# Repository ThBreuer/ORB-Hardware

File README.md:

# ORB-Hardware
OpenRoboticBoard: schematics, layout and documentation

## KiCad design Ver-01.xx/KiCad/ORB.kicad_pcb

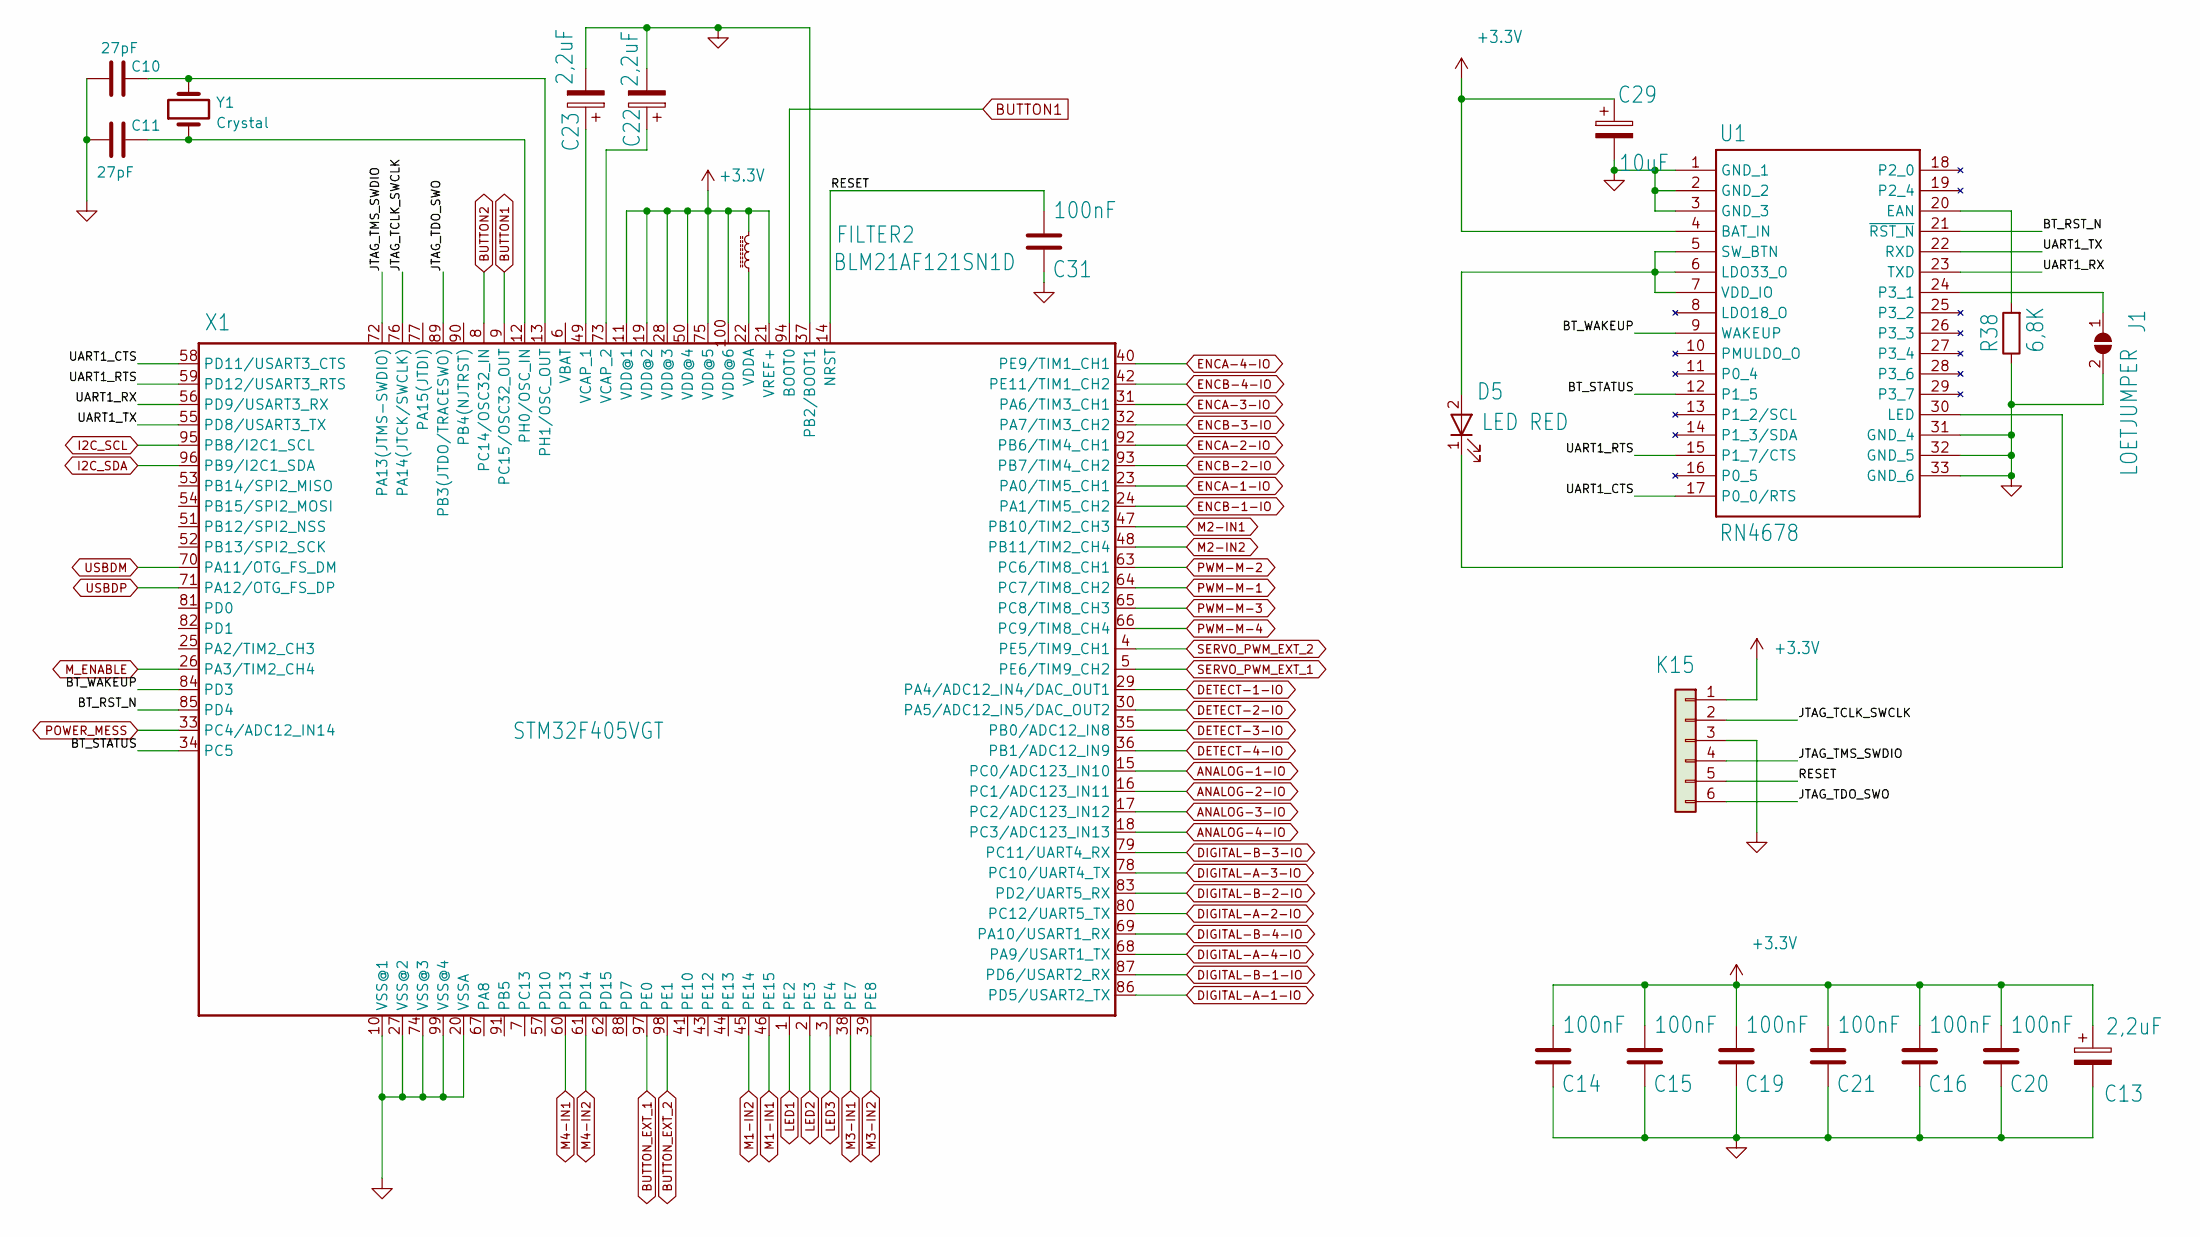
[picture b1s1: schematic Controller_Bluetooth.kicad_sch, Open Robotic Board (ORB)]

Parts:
C10, C11: 27pF; C_0805_2012Metric; MPN C0805C270K8HAC7800
C13, C22, C23: 2,2uF; CP_EIA-3216-10_Kemet-I; MPN T491A225K016AT
C14, C15, C16, C19, C20, C21, C31: 100nF; C_0805_2012Metric; MPN C0805C104K5RAC7800
C29: 10uF; CP_EIA-3528-12_Kemet-T; MPN T491B106M025AT
D5: LED RED; LED_0805_2012Metric; MPN QTLP630C7TR
FILTER2: BLM21AF121SN1D; L_0805_2012Metric; MPN BLM21AG121SN1D
J1: LOETJUMPER; SolderJumper-2_P1.3mm_Open_Pad1.0x1.5mm; MPN not mounted
K15: Stiftleiste_1x06; PinHeader_1x06_P2.54mm_Vertical; MPN not mounted
R38: 6,8K; R_0603_1608Metric; MPN RC0603FR-136K8L
U1: RN4678; MODULE_RN4678-V_RM100; MPN RN4678-V/RM113
X1: STM32F405VGT; LQFP-100_14x14mm_P0.5mm; MPN STM32F405VGT6
Y1: Crystal; Crystal_SMD_Abracon_ABM3-2Pin_5.0x3.2mm; MPN ECS-80-18-30-JGN-TR

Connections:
+3V3: C13.1, C14.2, C15.2, C16.2, C19.2, C20.2, C21.2, C29.1, FILTER2.2, K15.1, U1.4 (BAT_IN), X1.11 (VDD@1), X1.19 (VDD@2), X1.21 (VREF+), X1.28 (VDD@3), X1.50 (VDD@4), X1.75 (VDD@5), X1.100 (VDD@6); also elsewhere on the board
/Controller, Bluetooth/BT_RST_N: U1.21 (~RST_N), X1.85 (PD4)
/Controller, Bluetooth/BT_STATUS: U1.12 (P1_5), X1.34 (PC5)
/Controller, Bluetooth/BT_WAKEUP: U1.9 (WAKEUP), X1.84 (PD3)
/Controller, Bluetooth/JTAG_TCLK_SWCLK: K15.2, X1.76 (PA14(JTCK/SWCLK))
/Controller, Bluetooth/JTAG_TDO_SWO: K15.6, X1.89 (PB3(JTDO/TRACESWO))
/Controller, Bluetooth/JTAG_TMS_SWDIO: K15.4, X1.72 (PA13(JTMS-SWDIO))
/Controller, Bluetooth/RESET: C31.2, K15.5, X1.14 (NRST)
/Controller, Bluetooth/UART1_CTS: U1.17 (P0_0/RTS), X1.58 (PD11/USART3_CTS)
/Controller, Bluetooth/UART1_RTS: U1.15 (P1_7/CTS), X1.59 (PD12/USART3_RTS)
/Controller, Bluetooth/UART1_RX: U1.23 (TXD), X1.56 (PD9/USART3_RX)
/Controller, Bluetooth/UART1_TX: U1.22 (RXD), X1.55 (PD8/USART3_TX)
ANALOG-1-IO: X1.15 (PC0/ADC123_IN10); also elsewhere on the board
ANALOG-2-IO: X1.16 (PC1/ADC123_IN11); also elsewhere on the board
ANALOG-3-IO: X1.17 (PC2/ADC123_IN12); also elsewhere on the board
ANALOG-4-IO: X1.18 (PC3/ADC123_IN13); also elsewhere on the board
BUTTON1: X1.9 (PC15/OSC32_OUT), X1.94 (BOOT0); also elsewhere on the board
BUTTON2: X1.8 (PC14/OSC32_IN); also elsewhere on the board
BUTTON_EXT_1: X1.97 (PE0); also elsewhere on the board
BUTTON_EXT_2: X1.98 (PE1); also elsewhere on the board
DETECT-1-IO: X1.29 (PA4/ADC12_IN4/DAC_OUT1); also elsewhere on the board
DETECT-2-IO: X1.30 (PA5/ADC12_IN5/DAC_OUT2); also elsewhere on the board
DETECT-3-IO: X1.35 (PB0/ADC12_IN8); also elsewhere on the board
DETECT-4-IO: X1.36 (PB1/ADC12_IN9); also elsewhere on the board
DIGITAL-A-1-IO: X1.86 (PD5/USART2_TX); also elsewhere on the board
DIGITAL-A-2-IO: X1.80 (PC12/UART5_TX); also elsewhere on the board
DIGITAL-A-3-IO: X1.78 (PC10/UART4_TX); also elsewhere on the board
DIGITAL-A-4-IO: X1.68 (PA9/USART1_TX); also elsewhere on the board
DIGITAL-B-1-IO: X1.87 (PD6/USART2_RX); also elsewhere on the board
DIGITAL-B-2-IO: X1.83 (PD2/UART5_RX); also elsewhere on the board
DIGITAL-B-3-IO: X1.79 (PC11/UART4_RX); also elsewhere on the board
DIGITAL-B-4-IO: X1.69 (PA10/USART1_RX); also elsewhere on the board
ENCA-1-IO: X1.23 (PA0/TIM5_CH1); also elsewhere on the board
ENCA-2-IO: X1.92 (PB6/TIM4_CH1); also elsewhere on the board
ENCA-3-IO: X1.31 (PA6/TIM3_CH1); also elsewhere on the board
ENCA-4-IO: X1.40 (PE9/TIM1_CH1); also elsewhere on the board
ENCB-1-IO: X1.24 (PA1/TIM5_CH2); also elsewhere on the board
ENCB-2-IO: X1.93 (PB7/TIM4_CH2); also elsewhere on the board
ENCB-3-IO: X1.32 (PA7/TIM3_CH2); also elsewhere on the board
ENCB-4-IO: X1.42 (PE11/TIM1_CH2); also elsewhere on the board
GND: C10.1, C11.1, C13.2, C14.1, C15.1, C16.1, C19.1, C20.1, C21.1, C22.2, C23.2, C29.2, C31.1, J1.2 (B), K15.3, R38.1, U1.1 (GND_1), U1.2 (GND_2), U1.3 (GND_3), U1.31 (GND_4), U1.32 (GND_5), U1.33 (GND_6), X1.10 (VSS@1), X1.20 (VSSA), X1.27 (VSS@2), X1.37 (PB2/BOOT1), X1.74 (VSS@3), X1.99 (VSS@4); also elsewhere on the board
I2C_SCL: X1.95 (PB8/I2C1_SCL); also elsewhere on the board
I2C_SDA: X1.96 (PB9/I2C1_SDA); also elsewhere on the board
LED1: X1.1 (PE2); also elsewhere on the board
LED2: X1.2 (PE3); also elsewhere on the board
LED3: X1.3 (PE4); also elsewhere on the board
M1-IN1: X1.46 (PE15); also elsewhere on the board
M1-IN2: X1.45 (PE14); also elsewhere on the board
M2-IN1: X1.47 (PB10/TIM2_CH3); also elsewhere on the board
M2-IN2: X1.48 (PB11/TIM2_CH4); also elsewhere on the board
M3-IN1: X1.38 (PE7); also elsewhere on the board
M3-IN2: X1.39 (PE8); also elsewhere on the board
M4-IN1: X1.60 (PD13); also elsewhere on the board
M4-IN2: X1.61 (PD14); also elsewhere on the board
M_ENABLE: X1.26 (PA3/TIM2_CH4); also elsewhere on the board
unnamed: D5.2 (A), U1.5 (SW_BTN), U1.6 (LDO33_O), U1.7 (VDD_IO)
unnamed: D5.1 (K), U1.30 (LED)
unnamed: J1.1 (A), U1.24 (P3_1)
unnamed: R38.2, U1.20 (EAN)
unnamed: C11.2, X1.12 (PH0/OSC_IN), Y1.1
unnamed: C10.2, X1.13 (PH1/OSC_OUT), Y1.2
unnamed: C23.1, X1.49 (VCAP_1)
unnamed: C22.1, X1.73 (VCAP_2)
unnamed: FILTER2.1, X1.22 (VDDA)
POWER_MESS: X1.33 (PC4/ADC12_IN14); also elsewhere on the board
PWM-M-1: X1.64 (PC7/TIM8_CH2); also elsewhere on the board
PWM-M-2: X1.63 (PC6/TIM8_CH1); also elsewhere on the board
PWM-M-3: X1.65 (PC8/TIM8_CH3); also elsewhere on the board
PWM-M-4: X1.66 (PC9/TIM8_CH4); also elsewhere on the board
SERVO_PWM_EXT_1: X1.5 (PE6/TIM9_CH2); also elsewhere on the board
SERVO_PWM_EXT_2: X1.4 (PE5/TIM9_CH1); also elsewhere on the board
USBDM: X1.70 (PA11/OTG_FS_DM); also elsewhere on the board
USBDP: X1.71 (PA12/OTG_FS_DP); also elsewhere on the board

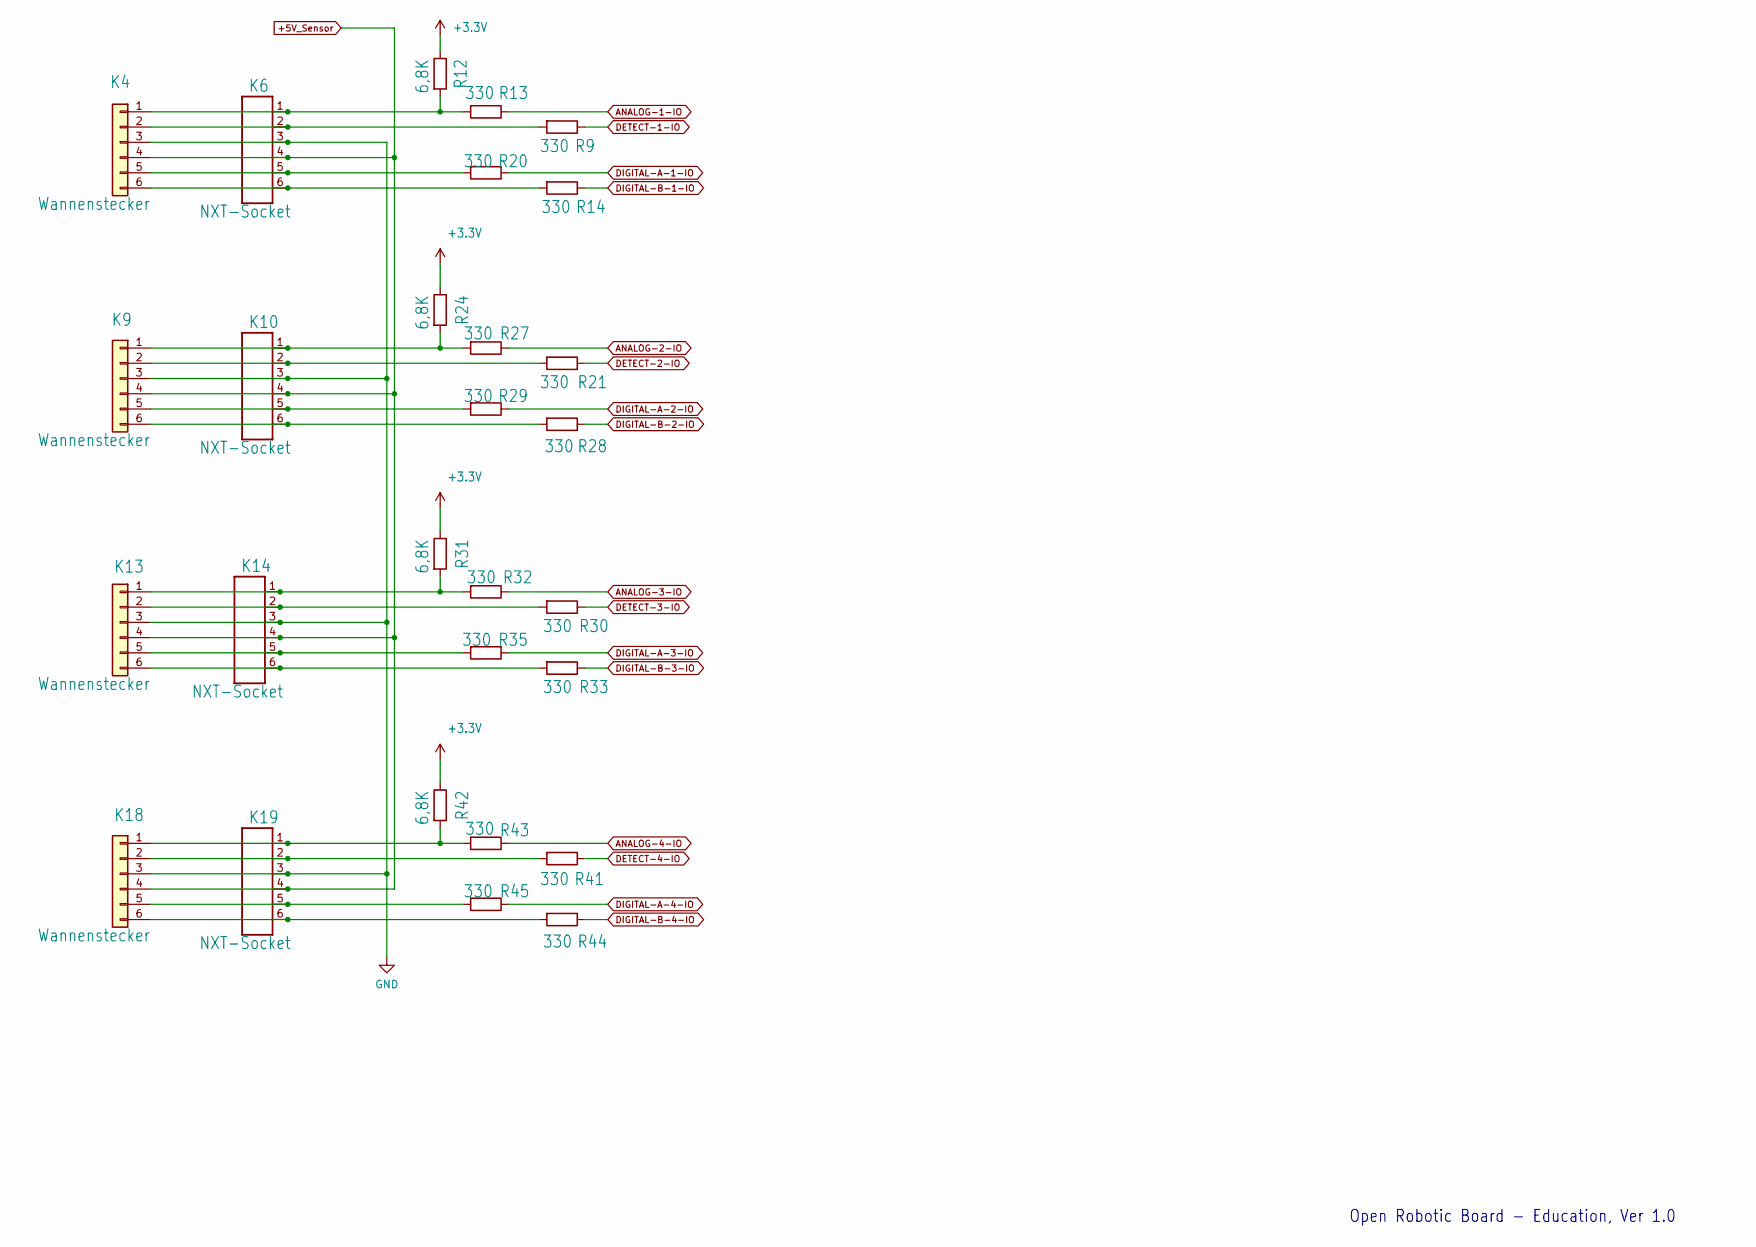
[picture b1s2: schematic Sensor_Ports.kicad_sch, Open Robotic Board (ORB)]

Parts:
K4, K9, K13, K18: Wannenstecker; IDC-Header_2x03_P2.54mm_Vertical; MPN not mounted
K6, K10, K14, K19: NXT-Socket; NXT-SOCKET; MPN NXT/EV3 Compatible (female) Sockets
R9, R13, R14, R20, R21, R27, R28, R29, R30, R32, R33, R35, R41, R43, R44, R45: 330; R_0603_1608Metric; MPN RC0603FR-10330RL
R12, R24, R31, R42: 6,8K; R_0603_1608Metric; MPN RC0603FR-136K8L

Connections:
+3V3: R12.1, R24.1, R31.1, R42.1; also elsewhere on the board
+5V_Sensor: K4.4, K6.4, K9.4, K10.4, K13.4, K14.4, K18.4, K19.4; also elsewhere on the board
ANALOG-1-IO: R13.1; also elsewhere on the board
ANALOG-2-IO: R27.1; also elsewhere on the board
ANALOG-3-IO: R32.1; also elsewhere on the board
ANALOG-4-IO: R43.1; also elsewhere on the board
DETECT-1-IO: R9.1; also elsewhere on the board
DETECT-2-IO: R21.1; also elsewhere on the board
DETECT-3-IO: R30.1; also elsewhere on the board
DETECT-4-IO: R41.1; also elsewhere on the board
DIGITAL-A-1-IO: R20.1; also elsewhere on the board
DIGITAL-A-2-IO: R29.1; also elsewhere on the board
DIGITAL-A-3-IO: R35.1; also elsewhere on the board
DIGITAL-A-4-IO: R45.1; also elsewhere on the board
DIGITAL-B-1-IO: R14.1; also elsewhere on the board
DIGITAL-B-2-IO: R28.1; also elsewhere on the board
DIGITAL-B-3-IO: R33.1; also elsewhere on the board
DIGITAL-B-4-IO: R44.1; also elsewhere on the board
GND: K4.3, K6.3, K9.3, K10.3, K13.3, K14.3, K18.3, K19.3; also elsewhere on the board
unnamed: K4.1, K6.1, R12.2, R13.2
unnamed: K4.2, K6.2, R9.2
unnamed: K4.5, K6.5, R20.2
unnamed: K4.6, K6.6, R14.2
unnamed: K9.1, K10.1, R24.2, R27.2
unnamed: K9.2, K10.2, R21.2
unnamed: K9.5, K10.5, R29.2
unnamed: K9.6, K10.6, R28.2
unnamed: K13.1, K14.1, R31.2, R32.2
unnamed: K13.2, K14.2, R30.2
unnamed: K13.5, K14.5, R35.2
unnamed: K13.6, K14.6, R33.2
unnamed: K18.1, K19.1, R42.2, R43.2
unnamed: K18.2, K19.2, R41.2
unnamed: K18.5, K19.5, R45.2
unnamed: K18.6, K19.6, R44.2

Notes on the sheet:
Open Robotic Board - Education, Ver 1.0

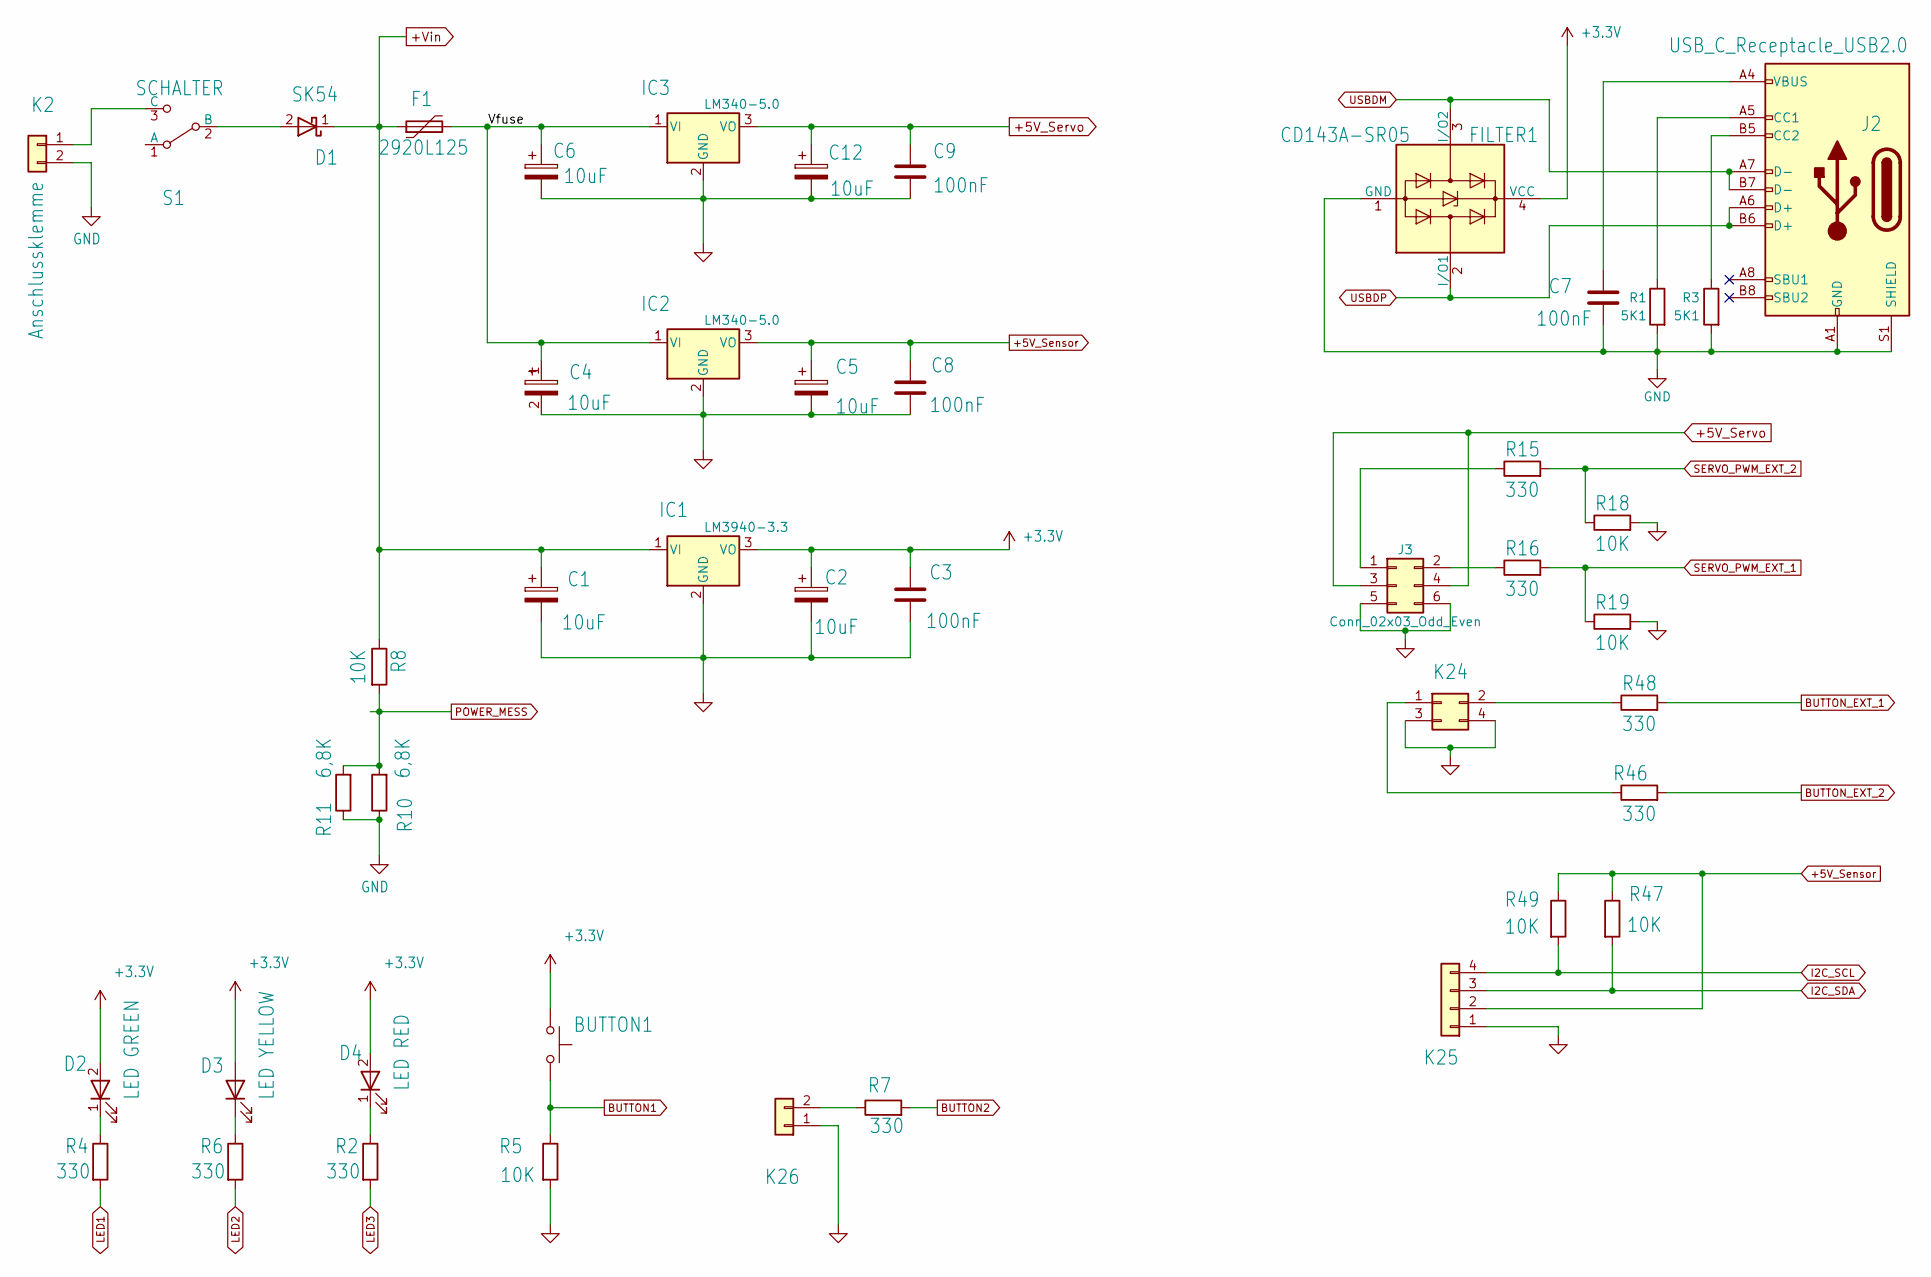
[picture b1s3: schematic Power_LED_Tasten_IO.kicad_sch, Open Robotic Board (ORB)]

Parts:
BUTTON1: Taster_SMD; SW_Push_1P1T_NO_6x6mm_H9.5mm; MPN PTS645SL70SMTR92 LFS
C1, C2, C4, C5, C6, C12: 10uF; CP_EIA-3528-12_Kemet-T; MPN T491B106M025AT
C3, C7, C8, C9: 100nF; C_0805_2012Metric; MPN C0805C104K5RAC7800
D1: SK54; D_SMB; MPN SK54B-LTP
D2: LED GREEN; LED_0805_2012Metric; MPN QTLP630C4TR
D3: LED YELLOW; LED_0805_2012Metric; MPN QTLP630C3TR
D4: LED RED; LED_0805_2012Metric; MPN QTLP630C7TR
F1: 2920L125; Fuse_2920_7451Metric; MPN 2920L125PR
FILTER1: CD143A-SR05; SOT-143; MPN CD143A-SR05LC
IC1: LM3940-3.3; SOT-223-3_TabPin2; MPN LM3940IMPX-3.3/NOPB
IC2, IC3: LM340-5.0; SOT-223-3_TabPin2; MPN LM340MPX-5.0/NOPB
J2: USB_C_Receptacle_USB2.0; USB_C_Receptacle_G-Switch_GT-USB-7010ASV; MPN GT-USB-7010ASV
J3: Conn_02x03_Odd_Even; PinHeader_2x03_P2.54mm_Horizontal; MPN PH2RA-06-UA
K2: Anschlussklemme; PinHeader_1x02_P2.54mm_Horizontal; MPN PH1RB-02-UA
K24: Stiftleiste_2x02; PinHeader_2x02_P2.54mm_Horizontal; MPN PH2RA-04-UA
K25: Stiftleiste_1x04; PinHeader_1x04_P2.54mm_Vertical; MPN not mounted
K26: Stiftleiste_1x02_G_2,54; PinHeader_1x02_P2.54mm_Vertical; MPN not mounted
R1, R3: 5K1; R_0603_1608Metric; MPN RC0603FR-135K1L
R2, R4, R6, R7, R15, R16, R46, R48: 330; R_0603_1608Metric; MPN RC0603FR-10330RL
R5, R8, R18, R19, R47, R49: 10K; R_0603_1608Metric; MPN RC0603FR-0710KP
R10, R11: 6,8K; R_0603_1608Metric; MPN RC0603FR-136K8L
S1: SCHALTER; SW_500SSP1S1M7QEA; MPN 500SSP1S1M7QEA

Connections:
+3V3: BUTTON1.1, C2.1, C3.2, D2.2 (A), D3.2 (A), D4.2 (A), FILTER1.4 (VCC), IC1.3 (VO); also elsewhere on the board
+5V_Sensor: C5.1, C8.2, IC2.3 (VO), K25.2, R47.1, R49.1; also elsewhere on the board
+5V_Servo: C9.2, C12.1, IC3.3 (VO), J3.3, J3.4
+Vin: C1.1, D1.1 (K), F1.1, IC1.1 (VI), R8.1; also elsewhere on the board
/Power, LED,Tasten, IO/Vfuse: C4.1, C6.1, F1.2, IC2.1 (VI), IC3.1 (VI)
BUTTON1: BUTTON1.2, R5.1; also elsewhere on the board
BUTTON2: R7.2; also elsewhere on the board
BUTTON_EXT_1: R48.2; also elsewhere on the board
BUTTON_EXT_2: R46.2; also elsewhere on the board
GND: C1.2, C2.2, C3.1, C4.2, C5.2, C6.2, C7.1, C8.1, C9.1, C12.2, FILTER1.1 (GND), IC1.2 (GND), IC2.2 (GND), IC3.2 (GND), J2.A1 (GND), J2.A12 (GND), J2.B1 (GND), J2.B12 (GND), J2.S1 (SHIELD), J3.5, J3.6, K2.2, K24.3, K24.4, K25.1, K26.1, R1.2, R3.2, R5.2, R10.1, R11.1, R18.2, R19.2; also elsewhere on the board
I2C_SCL: K25.4, R49.2; also elsewhere on the board
I2C_SDA: K25.3, R47.2; also elsewhere on the board
LED1: R4.2; also elsewhere on the board
LED2: R6.2; also elsewhere on the board
LED3: R2.2; also elsewhere on the board
unnamed: C7.2, J2.A4 (VBUS), J2.A9 (VBUS), J2.B4 (VBUS), J2.B9 (VBUS)
unnamed: D1.2 (A), S1.2 (B)
unnamed: D2.1 (K), R4.1
unnamed: D3.1 (K), R6.1
unnamed: D4.1 (K), R2.1
unnamed: J2.A5 (CC1), R1.1
unnamed: J2.B5 (CC2), R3.1
unnamed: J3.1, R15.1
unnamed: J3.2, R16.1
unnamed: K2.1, S1.3 (C)
unnamed: K24.1, R46.1
unnamed: K24.2, R48.1
unnamed: K26.2, R7.1
POWER_MESS: R8.2, R10.2, R11.2; also elsewhere on the board
SERVO_PWM_EXT_1: R16.2, R19.1; also elsewhere on the board
SERVO_PWM_EXT_2: R15.2, R18.1; also elsewhere on the board
USBDM: FILTER1.3 (I/O2), J2.A7 (D-), J2.B7 (D-); also elsewhere on the board
USBDP: FILTER1.2 (I/O1), J2.A6 (D+), J2.B6 (D+); also elsewhere on the board

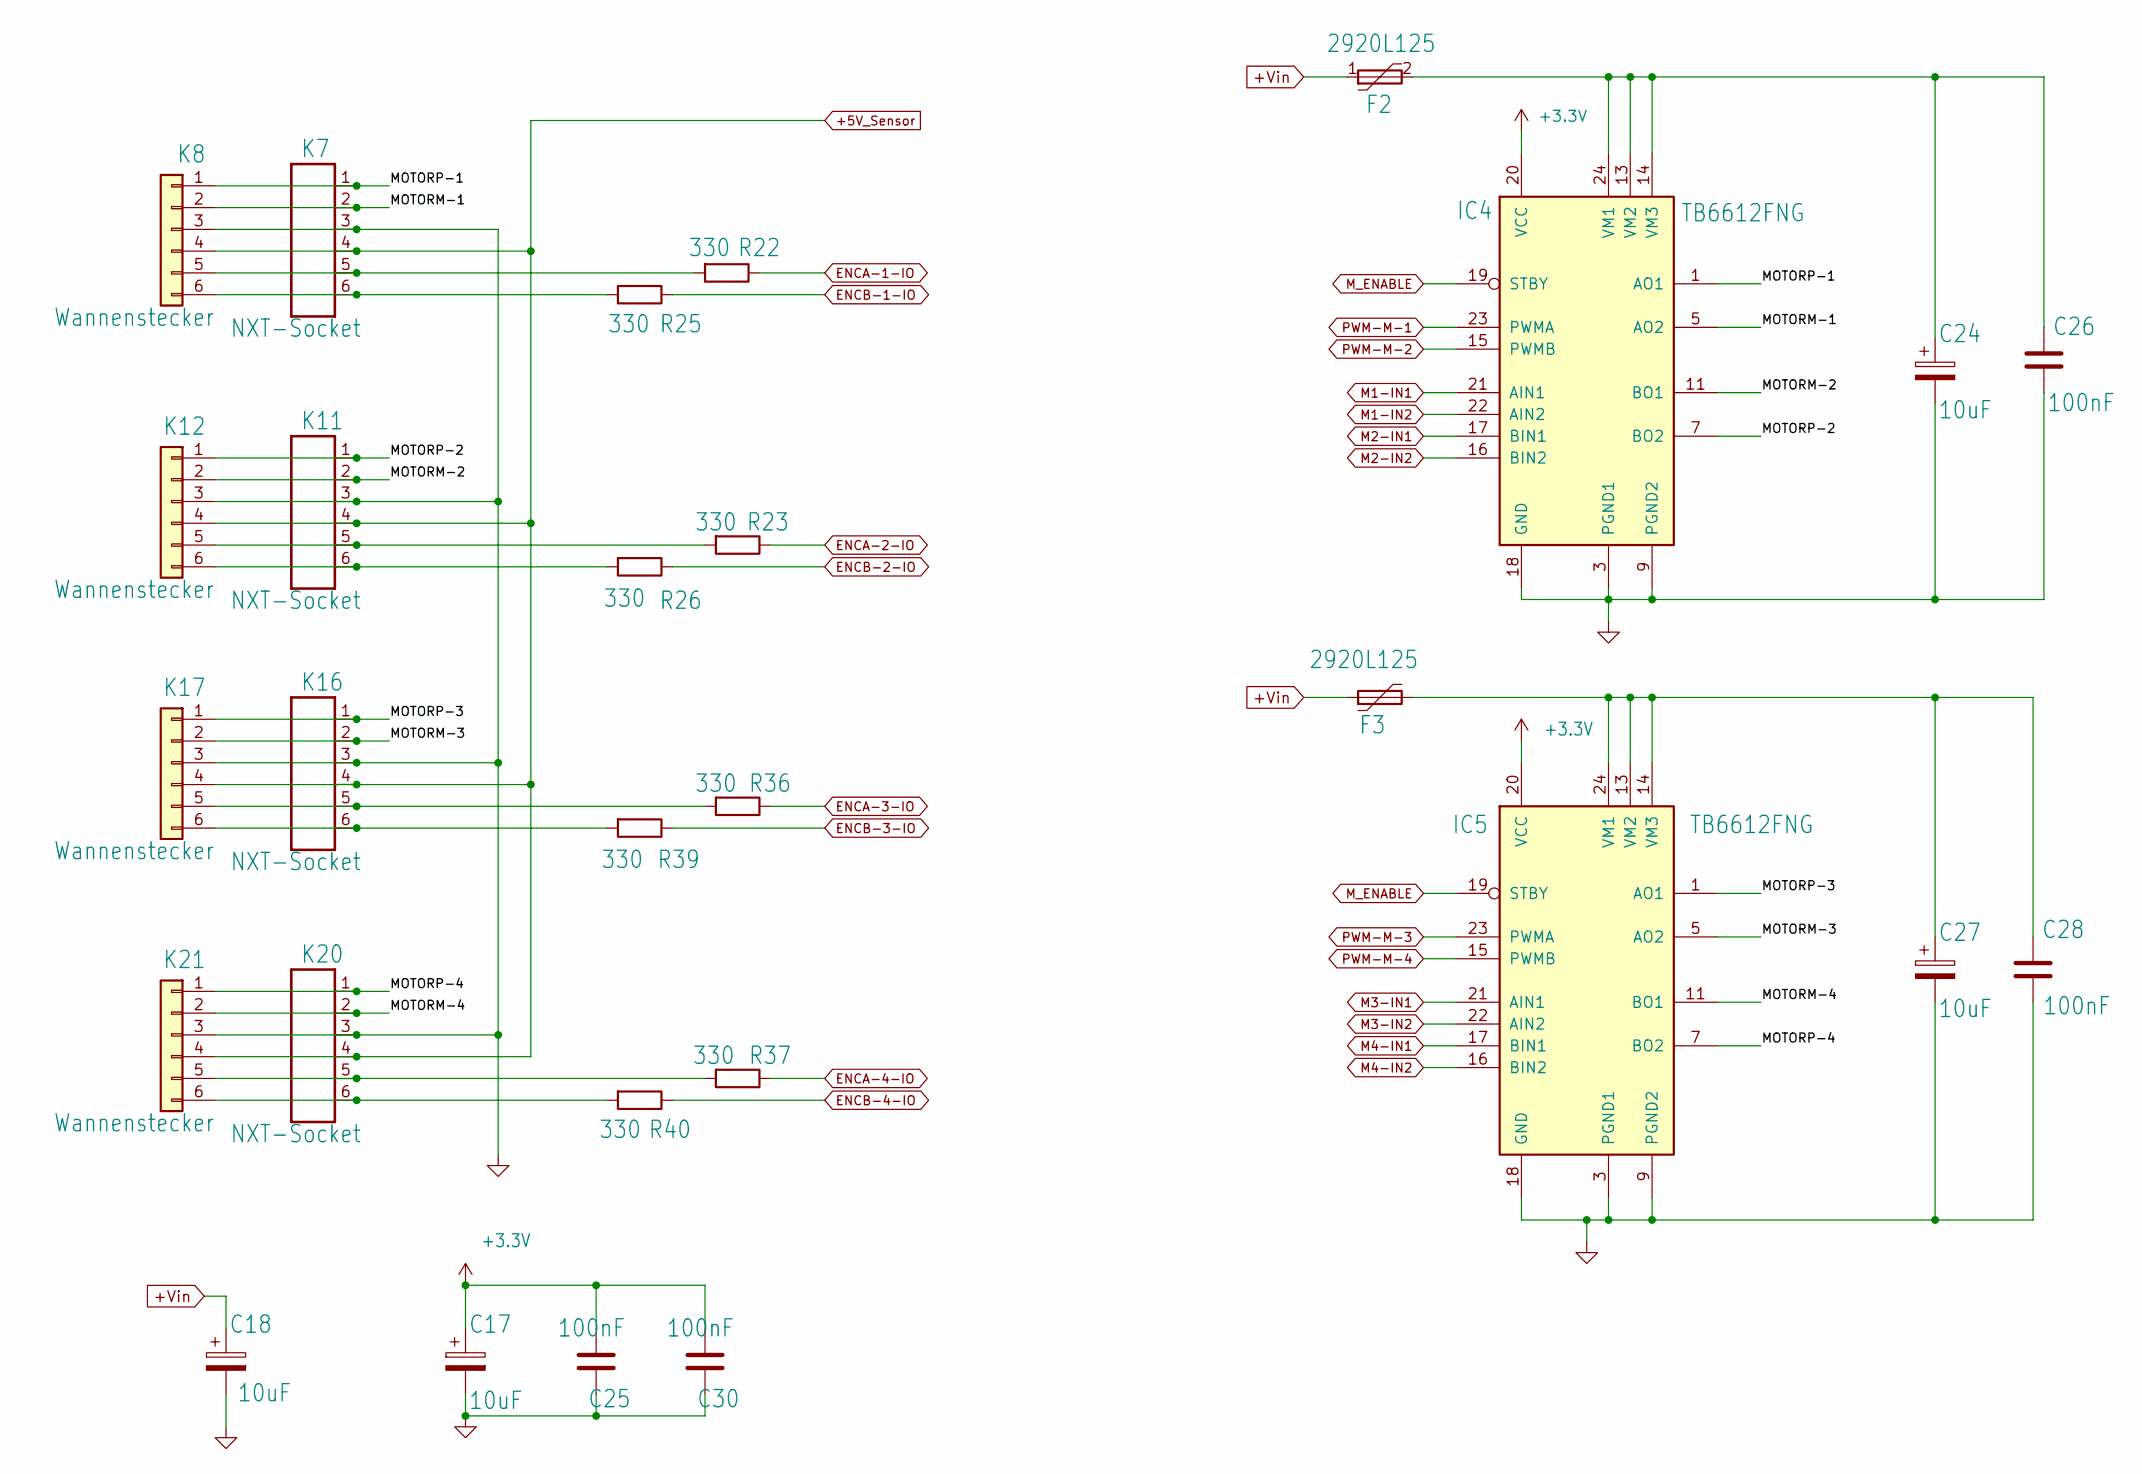
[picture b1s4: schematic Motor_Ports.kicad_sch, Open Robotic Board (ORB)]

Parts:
C17, C18, C24, C27: 10uF; CP_EIA-3528-12_Kemet-T; MPN T491B106M025AT
C25, C26, C28, C30: 100nF; C_0805_2012Metric; MPN C0805C104K5RAC7800
F2, F3: 2920L125; Fuse_2920_7451Metric; MPN 2920L125PR
IC4, IC5: TB6612FNG; SSOP-24_5.3x8.2mm_P0.65mm; MPN TB6612FNG,C,8,EL
K7, K11, K16, K20: NXT-Socket; NXT-SOCKET; MPN NXT/EV3 Compatible (female) Sockets
K8, K12, K17, K21: Wannenstecker; IDC-Header_2x03_P2.54mm_Vertical; MPN not mounted
R22, R23, R25, R26, R36, R37, R39, R40: 330; R_0603_1608Metric; MPN RC0603FR-10330RL

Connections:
+3V3: C17.1, C25.2, C30.2, IC4.20 (VCC), IC5.20 (VCC); also elsewhere on the board
+5V_Sensor: K7.4, K8.4, K11.4, K12.4, K16.4, K17.4, K20.4, K21.4; also elsewhere on the board
+Vin: C18.1, F2.1, F3.1; also elsewhere on the board
/Motor-Ports/MOTORM-1: IC4.5 (AO2), IC4.6 (AO2), K7.2, K8.2
/Motor-Ports/MOTORM-2: IC4.11 (BO1), IC4.12 (BO1), K11.2, K12.2
/Motor-Ports/MOTORM-3: IC5.5 (AO2), IC5.6 (AO2), K16.2, K17.2
/Motor-Ports/MOTORM-4: IC5.11 (BO1), IC5.12 (BO1), K20.2, K21.2
/Motor-Ports/MOTORP-1: IC4.1 (AO1), IC4.2 (AO1), K7.1, K8.1
/Motor-Ports/MOTORP-2: IC4.7 (BO2), IC4.8 (BO2), K11.1, K12.1
/Motor-Ports/MOTORP-3: IC5.1 (AO1), IC5.2 (AO1), K16.1, K17.1
/Motor-Ports/MOTORP-4: IC5.7 (BO2), IC5.8 (BO2), K20.1, K21.1
ENCA-1-IO: R22.1; also elsewhere on the board
ENCA-2-IO: R23.1; also elsewhere on the board
ENCA-3-IO: R36.1; also elsewhere on the board
ENCA-4-IO: R37.1; also elsewhere on the board
ENCB-1-IO: R25.1; also elsewhere on the board
ENCB-2-IO: R26.1; also elsewhere on the board
ENCB-3-IO: R39.1; also elsewhere on the board
ENCB-4-IO: R40.1; also elsewhere on the board
GND: C17.2, C18.2, C24.2, C25.1, C26.1, C27.2, C28.1, C30.1, IC4.3 (PGND1), IC4.4 (PGND1), IC4.9 (PGND2), IC4.10 (PGND2), IC4.18 (GND), IC5.3 (PGND1), IC5.4 (PGND1), IC5.9 (PGND2), IC5.10 (PGND2), IC5.18 (GND), K7.3, K8.3, K11.3, K12.3, K16.3, K17.3, K20.3, K21.3; also elsewhere on the board
M1-IN1: IC4.21 (AIN1); also elsewhere on the board
M1-IN2: IC4.22 (AIN2); also elsewhere on the board
M2-IN1: IC4.17 (BIN1); also elsewhere on the board
M2-IN2: IC4.16 (BIN2); also elsewhere on the board
M3-IN1: IC5.21 (AIN1); also elsewhere on the board
M3-IN2: IC5.22 (AIN2); also elsewhere on the board
M4-IN1: IC5.17 (BIN1); also elsewhere on the board
M4-IN2: IC5.16 (BIN2); also elsewhere on the board
M_ENABLE: IC4.19 (STBY), IC5.19 (STBY); also elsewhere on the board
unnamed: C24.1, C26.2, F2.2, IC4.13 (VM2), IC4.14 (VM3), IC4.24 (VM1)
unnamed: C27.1, C28.2, F3.2, IC5.13 (VM2), IC5.14 (VM3), IC5.24 (VM1)
unnamed: K7.5, K8.5, R22.2
unnamed: K7.6, K8.6, R25.2
unnamed: K11.5, K12.5, R23.2
unnamed: K11.6, K12.6, R26.2
unnamed: K16.5, K17.5, R36.2
unnamed: K16.6, K17.6, R39.2
unnamed: K20.5, K21.5, R37.2
unnamed: K20.6, K21.6, R40.2
PWM-M-1: IC4.23 (PWMA); also elsewhere on the board
PWM-M-2: IC4.15 (PWMB); also elsewhere on the board
PWM-M-3: IC5.23 (PWMA); also elsewhere on the board
PWM-M-4: IC5.15 (PWMB); also elsewhere on the board

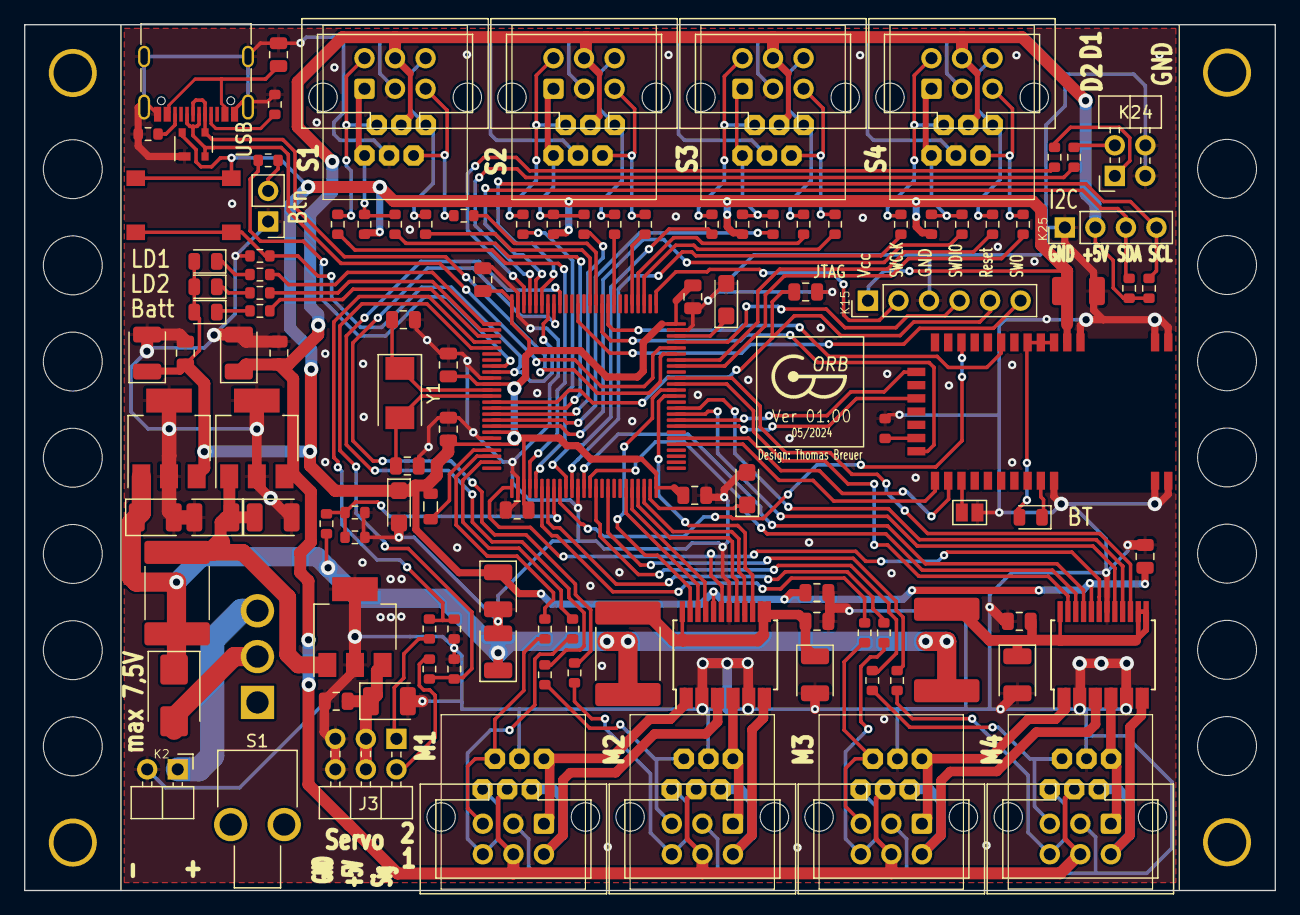
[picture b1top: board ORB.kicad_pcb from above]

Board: 2 copper layers, 104.0 x 72.0 mm, 123 parts (0 on the bottom side), 124 nets.

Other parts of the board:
Logo**: Logo

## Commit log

2023-10-11 initial version
2023-10-11 Update LICENSE
2023-10-11 moved
2023-11-10 kicad files
2023-11-12 New Logo
2023-11-12 Snap to grid
2023-11-12 New R in OSC
2023-11-17 Kleinere Optimierungen
2023-11-23 R (Crystal) raus, C (Reset) hinzu
2024-02-01 Review
    - New Crystal
    - GND plane on front side
2024-02-01 Abstand MotorX-Y kleiner
2024-02-16 Update KiCad 7.x, Crystal changed
2024-05-07 After production test
    Footprint D1 and Y1 changed.
    LED shunt R=330
2024-05-07 USB connector changed
